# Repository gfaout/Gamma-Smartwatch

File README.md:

# Gamma-Smartwatch
Smartwatch designed in Summer of 2020

Version A (basic version):

Top Board Unfilled:

Top Board Filled:

Bottom Board Unfilled:

Bottom Board Filled:

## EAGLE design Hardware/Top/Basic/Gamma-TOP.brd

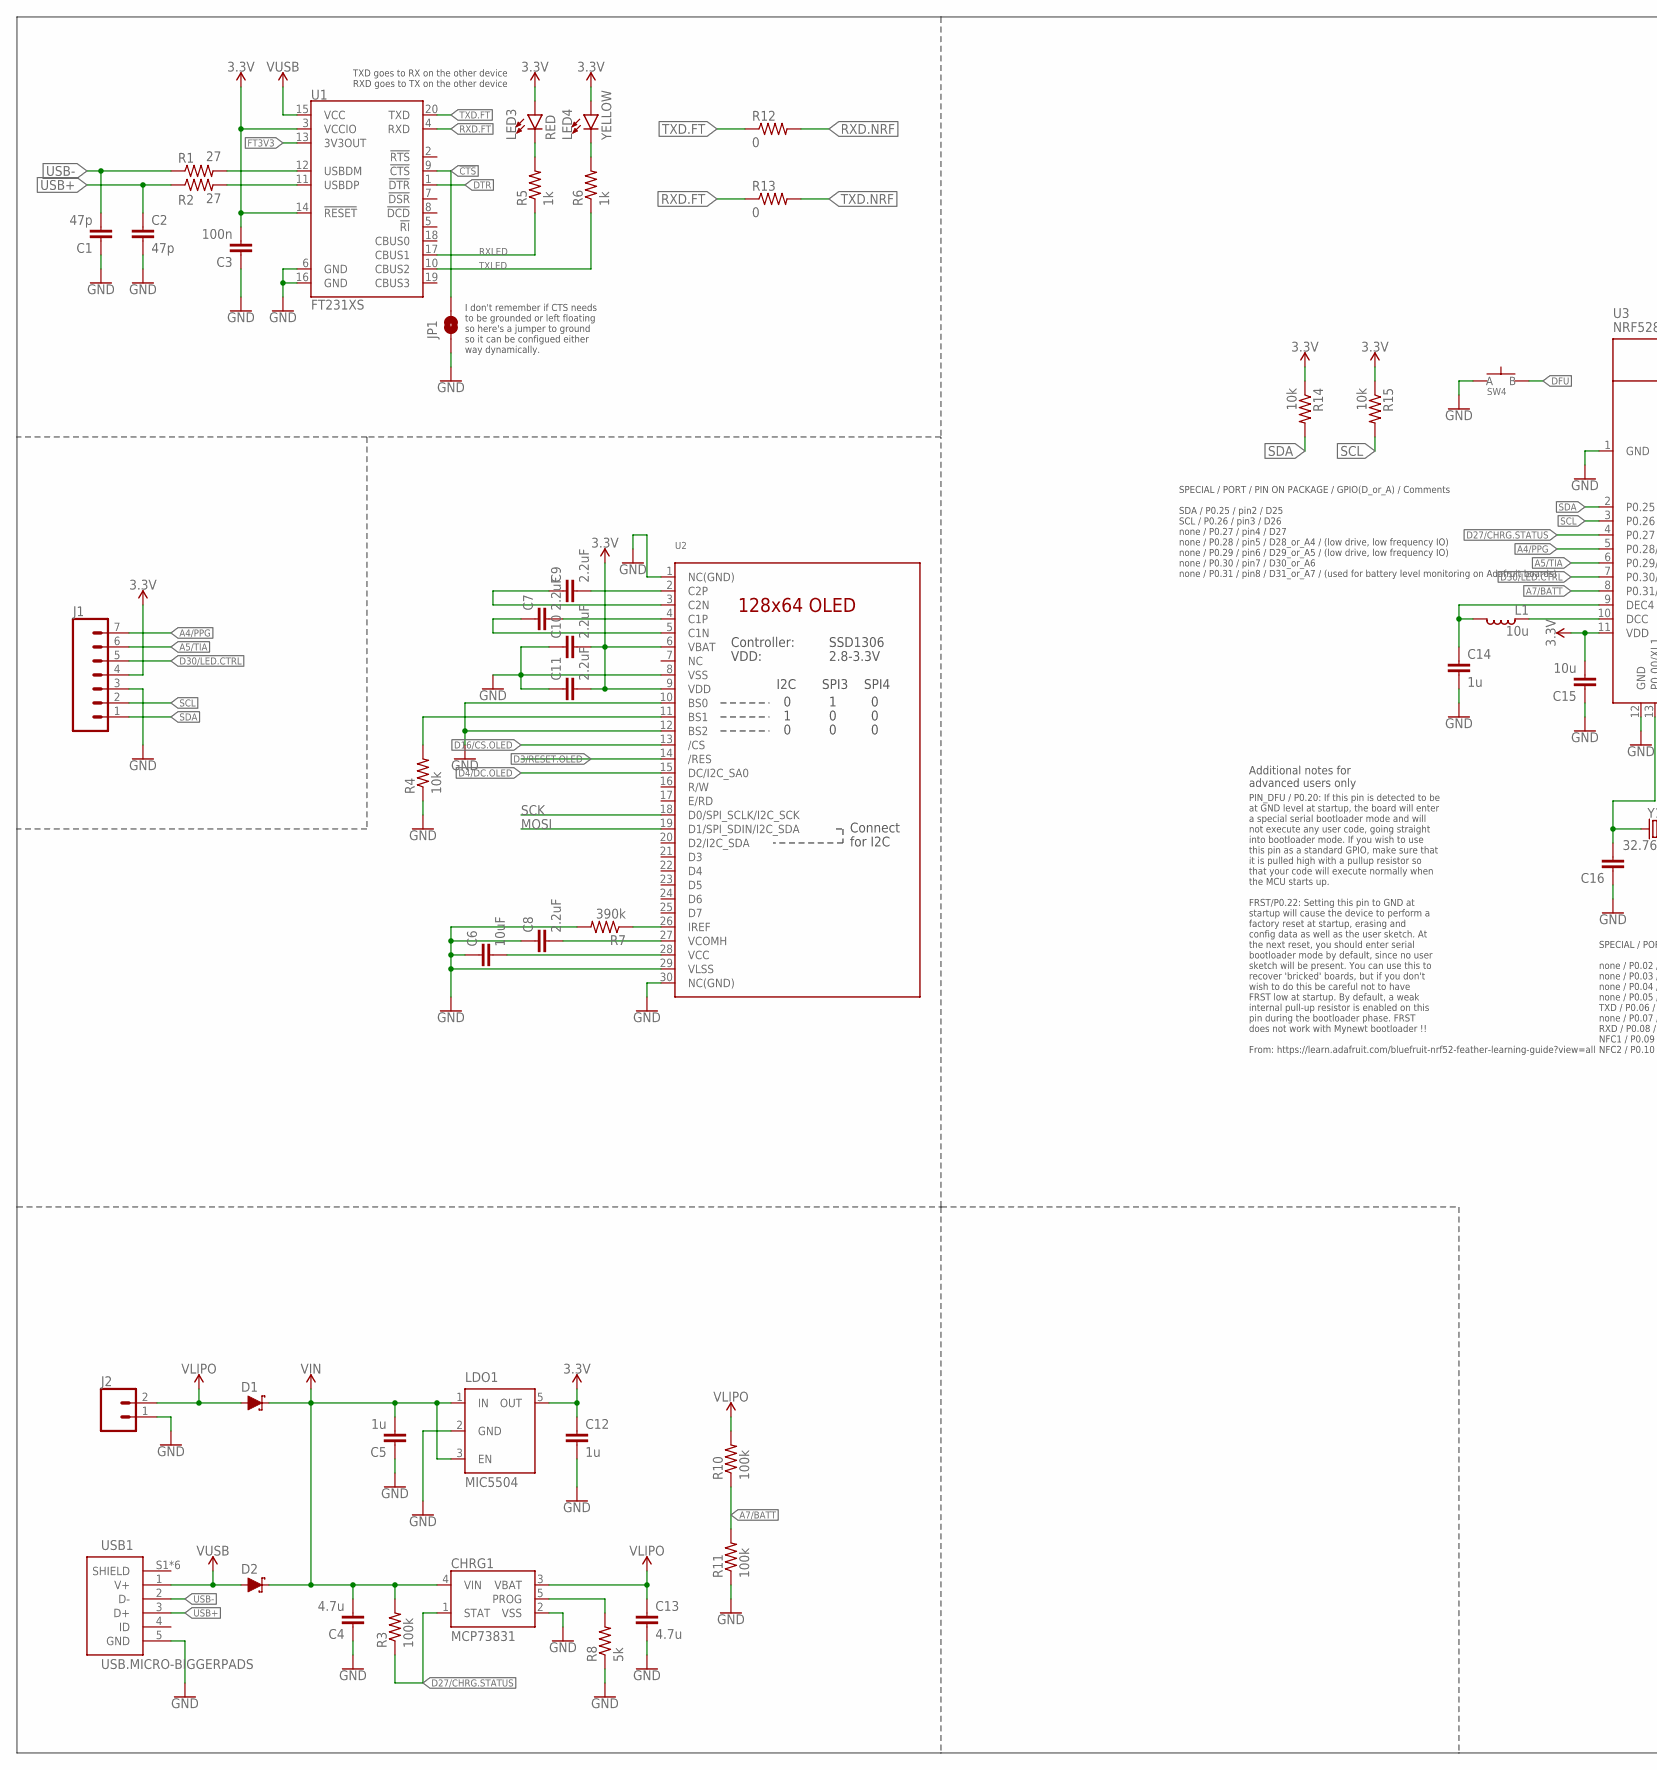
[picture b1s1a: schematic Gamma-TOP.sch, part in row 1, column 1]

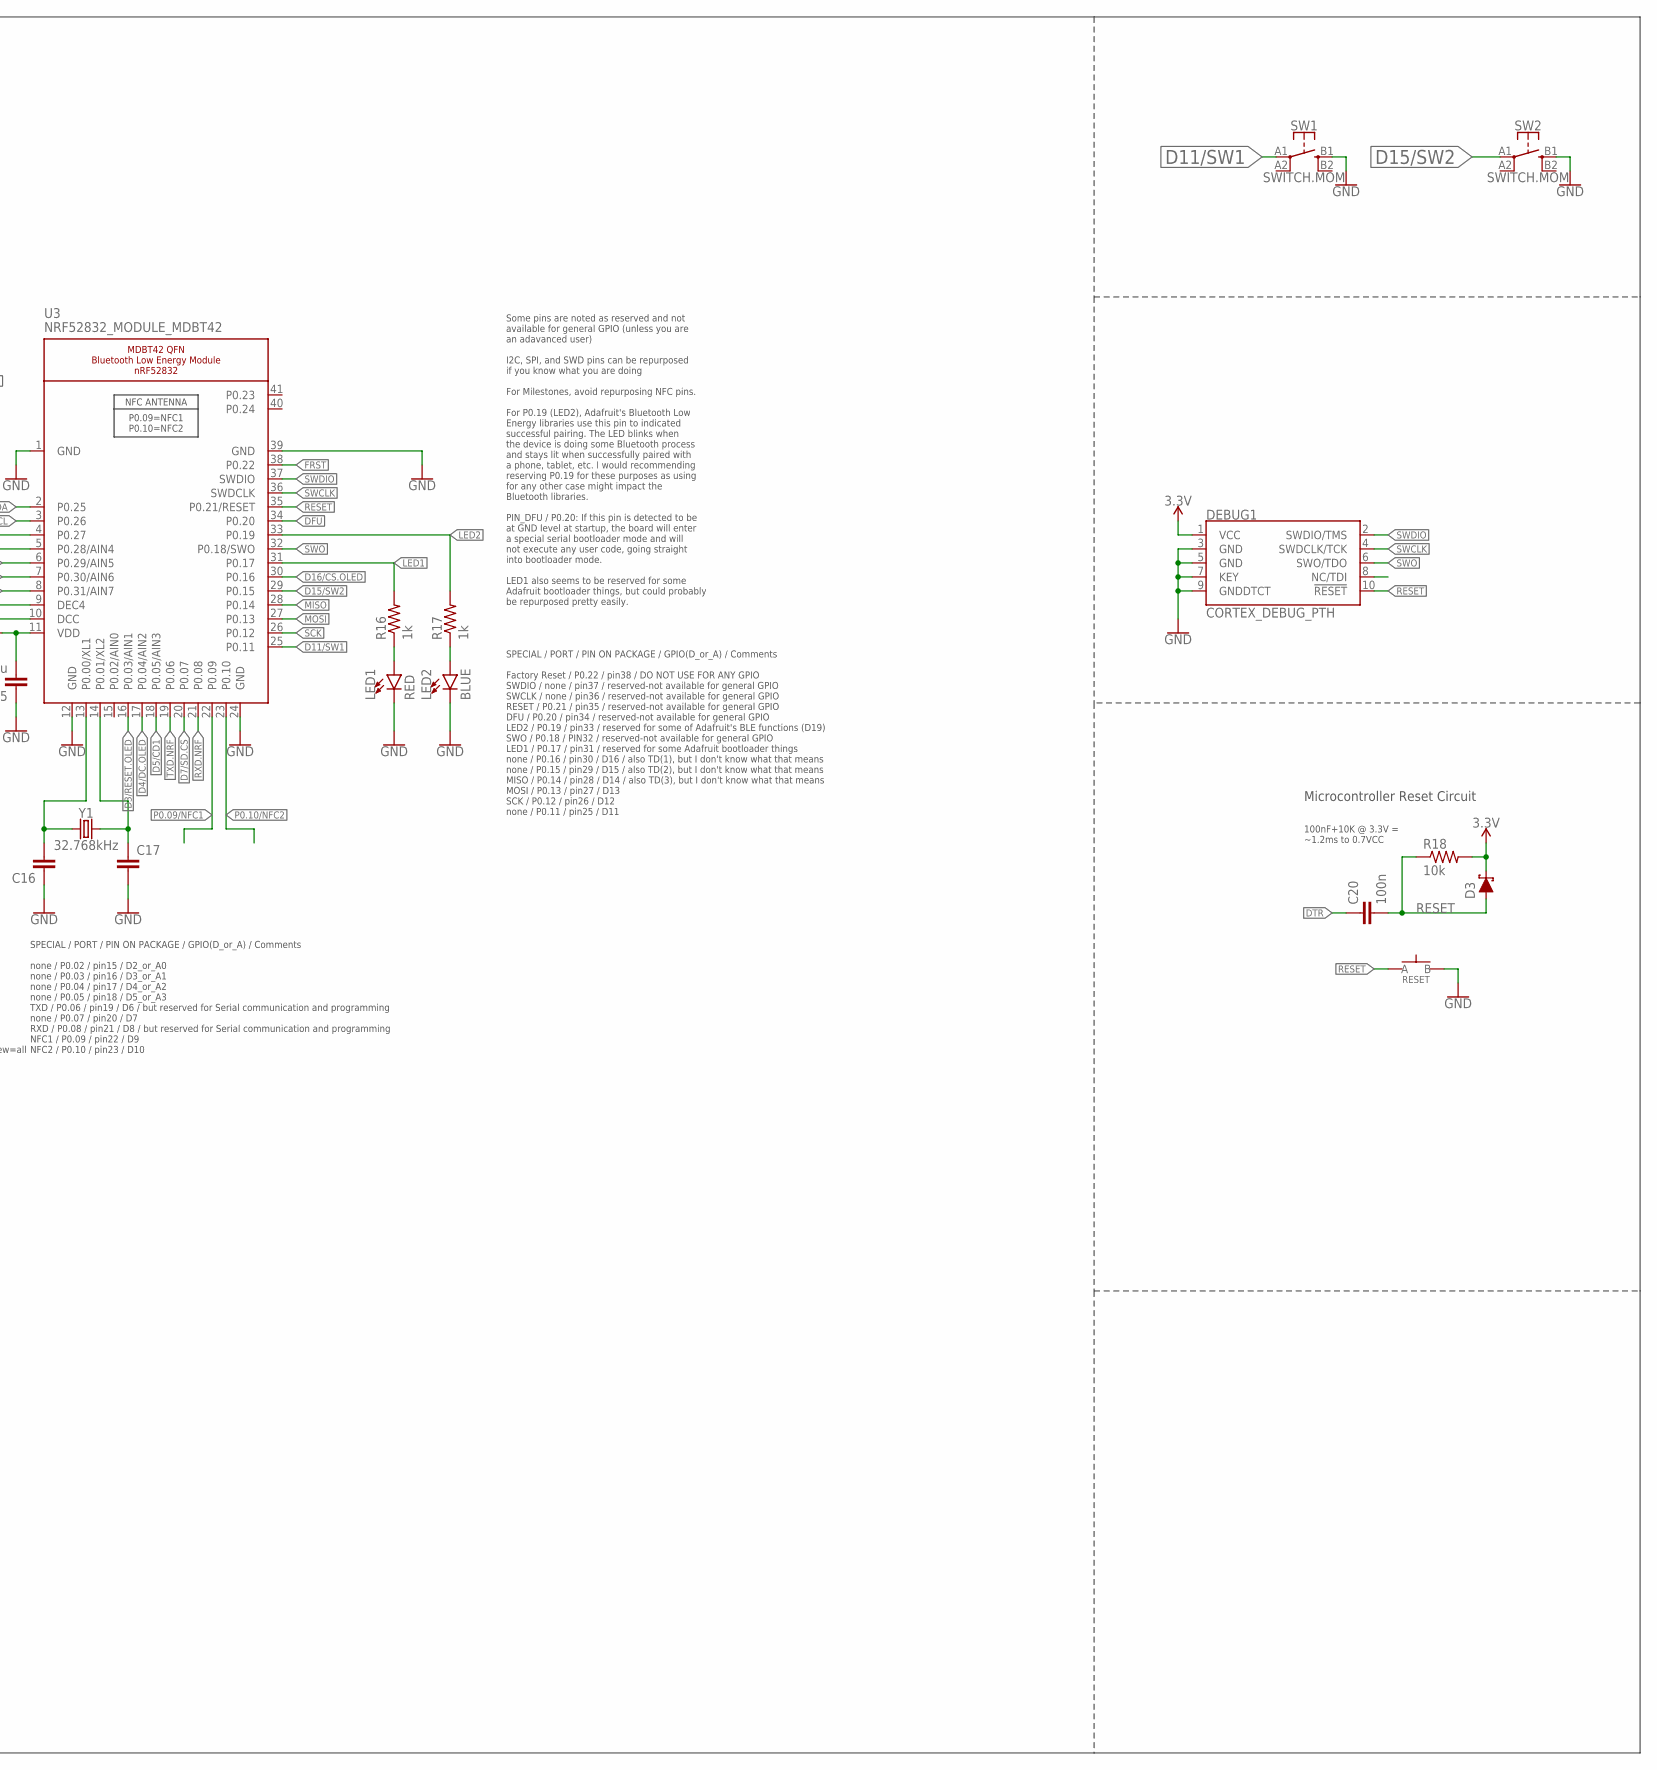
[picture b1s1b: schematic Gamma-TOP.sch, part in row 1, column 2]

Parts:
C1, C2: 47p; C0603
C3, C20: 100n; C0603
C4, C13: 4.7u; C0603
C5, C12, C14: 1u; C0603
C6: 10uF; C0603
C7, C9, C10, C11: 2.2uF; C0402
C8: 2.2uF; C0603
C15: 10u; C0805
C16, C17: CAPACITOR0603; C0603
CHRG1: MCP73831; SOT23-5
D1, D2, D3: SCHOTTKY-USC; USC
DEBUG1: CORTEX_DEBUG_PTH; 2X5-PTH-1.27MM
J1: CONN_07-1.27MM; 1X07_1.27MM
J2: CONN_02; 1X02
JP1: JUMPER-SMT_2_NO_SILK; SMT-JUMPER_2_NO_SILK
L1: 10u; L0603
LDO1: MIC5504; SOT23-5
LED1, LED3: RED; LED-0603
LED2: BLUE; LED-0603
LED4: YELLOW; LED-0603
R1, R2: 27; R0603
R3, R10, R11: 100k; R0603
R4, R14, R15, R18: 10k; R0603
R5, R6, R16, R17: 1k; R0603
R7: 390k; R0603
R8: 5k; R0603
R12, R13: 0; R0603
RESET: SPST-PTS830GG140-COPY.1-3; BUTTON-GULLWING
SW1, SW2: SWITCH.MOM; TACTILE_SWITCH_SMD_6.2MM_TALL
SW4: SPST-PTS830GG140-COPY.1-3; BUTTON-GULLWING
U1: FT231XS; SSOP20_L
U2: DISP_OLED_UG-2864HSWEG01-NO-WRAPAROUND; UG-2864HSWEG01_0.96IN_NO-WRAPAROUND
U3: NRF52832_MODULE_MDBT42; BLE_MODULE_RAYTAC_MDBT42
USB1: USB.MICRO-BIGGERPADS; USB-MICRO-01.BIGGERPADS
Y1: 32.768kHz; 2-SMD.NOLEAD.2.0MMTO1.2MM

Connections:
3.3V: C3.2, C10.2, C11.2, C12.1, C15.2, D3.- (C), DEBUG1.1 (VCC), J1.4, LDO1.5 (OUT), LED3.A, LED4.A, R14.1, R15.1, R18.2, U1.3 (VCCIO), U1.14 (!RESET), U2.6 (VBAT), U2.9 (VDD), U3.11 (VDD)
!CTS: JP1.2, U1.9 (!CTS)
A4/PPG: J1.7, U3.5 (P0.28/AIN4)
A5/TIA: J1.6, U3.6 (P0.29/AIN5)
A7/BATT: R10.1, R11.2, U3.8 (P0.31/AIN7)
D3/RESET.OLED: U2.14 (/RES), U3.16 (P0.03/AIN1)
D4/DC.OLED: U2.15 (DC/I2C_SA0), U3.17 (P0.04/AIN2)
D5/CD1: U3.18 (P0.05/AIN3)
D7/SD.CS: U3.20 (P0.07)
D11/SW1: SW1.A1 (1), U3.25 (P0.11)
D15/SW2: SW2.A1 (1), U3.29 (P0.15)
D16/CS.OLED: U2.13 (/CS), U3.30 (P0.16)
D27/CHRG.STATUS: CHRG1.1 (STAT), R3.1, U3.4 (P0.27)
D30/LED.CTRL: J1.5, U3.7 (P0.30/AIN6)
DFU: SW4.3 (B), U3.34 (P0.20)
DTR: C20.1, U1.1 (!DTR)
FRST: U3.38 (P0.22)
FT3V3: U1.13 (3V3OUT)
GND: C1.1, C2.2, C3.1, C4.1, C5.1, C6.1, C8.1, C10.1, C11.1, C12.2, C13.2, C14.2, C15.1, C16.1, C17.2, CHRG1.2 (VSS), DEBUG1.3 (GND), DEBUG1.5 (GND), DEBUG1.7 (KEY), DEBUG1.9 (GNDDTCT), J1.3, J2.1, JP1.1, LDO1.2 (GND), LED1.C, LED2.C, R4.1, R7.2, R8.1, R11.1, RESET.3 (B), SW1.B1 (3), SW2.B1 (3), SW4.1 (A), U1.6 (GND), U1.16 (GND), U2.1 (NC(GND)), U2.8 (VSS), U2.10 (BS0), U2.12 (BS2), U2.29 (VLSS), U2.30 (NC(GND)), U3.1 (GND), U3.12 (GND), U3.24 (GND), U3.39 (GND), USB1.5 (GND)
LED1: R16.2, U3.31 (P0.17)
LED2: R17.2, U3.33 (P0.19)
MISO: U3.28 (P0.14)
MOSI: U2.19 (D1/SPI_SDIN/I2C_SDA), U3.27 (P0.13)
unnamed: R4.2, U2.11 (BS1)
unnamed: R7.1, U2.26 (IREF)
unnamed: C9.2, U2.2 (C2P)
unnamed: C16.2, U3.13 (P0.00/XL1), Y1.P$1 (1)
unnamed: C9.1, U2.3 (C2N)
unnamed: C17.1, U3.14 (P0.01/XL2), Y1.P$2 (2)
unnamed: C7.2, U2.4 (C1P)
unnamed: C7.1, U2.5 (C1N)
unnamed: LED1.A, R16.1
unnamed: LED2.A, R17.1
unnamed: L1.1, U3.10 (DCC)
unnamed: C14.1, L1.2, U3.9 (DEC4)
unnamed: C6.2, U2.28 (VCC)
unnamed: C8.2, U2.27 (VCOMH)
unnamed: CHRG1.5 (PROG), R8.2
unnamed: R1.2, U1.12 (USBDM)
unnamed: R2.2, U1.11 (USBDP)
unnamed: LED3.C, R5.2
unnamed: LED4.C, R6.2
P0.09/NFC1: U3.22 (P0.09)
P0.10/NFC2: U3.23 (P0.10)
RESET: C20.2, D3.+ (A), DEBUG1.10 (!RESET), R18.1, RESET.1 (A), U3.35 (P0.21/RESET)
RXD.FT: R13.1, U1.4 (RXD)
RXD.NRF: R12.2, U3.21 (P0.08)
RXLED: R5.1, U1.17 (CBUS1)
SCK: U2.18 (D0/SPI_SCLK/I2C_SCK), U3.26 (P0.12)
SCL: J1.2, R15.2, U3.3 (P0.26)
SDA: J1.1, R14.2, U3.2 (P0.25)
SWCLK: DEBUG1.4 (SWDCLK/TCK), U3.36 (SWDCLK)
SWDIO: DEBUG1.2 (SWDIO/TMS), U3.37 (SWDIO)
SWO: DEBUG1.6 (SWO/TDO), U3.32 (P0.18/SWO)
TXD.FT: R12.1, U1.20 (TXD)
TXD.NRF: R13.2, U3.19 (P0.06)
TXLED: R6.1, U1.10 (CBUS2)
USB+: C2.1, R2.1, USB1.3 (D+)
USB-: C1.2, R1.1, USB1.2 (D-)
VIN: C4.2, C5.2, CHRG1.4 (VIN), D1.- (C), D2.- (C), LDO1.1 (IN), LDO1.3 (EN), R3.2
VLIPO: C13.1, CHRG1.3 (VBAT), D1.+ (A), J2.2, R10.2
V_USB: D2.+ (A), U1.15 (VCC), USB1.1 (V+)

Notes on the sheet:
Microcontroller Reset Circuit
100nF+10K @ 3.3V = ~1.2ms to 0.7VCC
SPECIAL / PORT / PIN ON PACKAGE / GPIO(D_or_A) / Comments SDA / P0.25 / pin2 / D25 SCL / P0.26 / pin3 / D26 none / P0.27 / pin4 / D27 none / P0.28 / pin5 / D28_or_A4 / (low drive, low frequency IO) none / P0.29 / pin6 / D29_or_A5 / (low drive, low frequency IO) none / P0.30 / pin7 / D30_or_A6 none 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
SPECIAL / PORT / PIN ON PACKAGE / GPIO(D_or_A) / Comments none / P0.02 / pin15 / D2_or_A0 none / P0.03 / pin16 / D3_or_A1 none / P0.04 / pin17 / D4_or_A2 none / P0.05 / pin18 / D5_or_A3 TXD / P0.06 / pin19 / D6 / but reserved for Serial communication and programming none / P0.07 / pin20 / D7 RXD / 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
SPECIAL / PORT / PIN ON PACKAGE / GPIO(D_or_A) / Comments Factory Reset / P0.22 / pin38 / DO NOT USE FOR ANY GPIO SWDIO / none / pin37 / reserved-not available for general GPIO SWCLK / none / pin36 / reserved-not available for general GPIO RESET / P0.21 / pin35 / reserved-not available for general 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
Some pins are noted as reserved and not available for general GPIO (unless you are an adavanced user) I2C, SPI, and SWD pins can be repurposed if you know what you are doing For Milestones, avoid repurposing NFC pins. For P0.19 (LED2), Adafruit's Bluetooth Low Energy libraries use this pin to indic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
PIN_DFU / P0.20: If this pin is detected to be at GND level at startup, the board will enter a special serial bootloader mode and will not execute any user code, going straight into bootloader mode. If you wish to use this pin as a standard GPIO, make sure that it is pulled high with a pullup resis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
Additional notes for advanced users only
TXD goes to RX on the other device RXD goes to TX on the other device
I don't remember if CTS needs to be grounded or left floating so here's a jumper to ground so it can be configued either way dynamically.

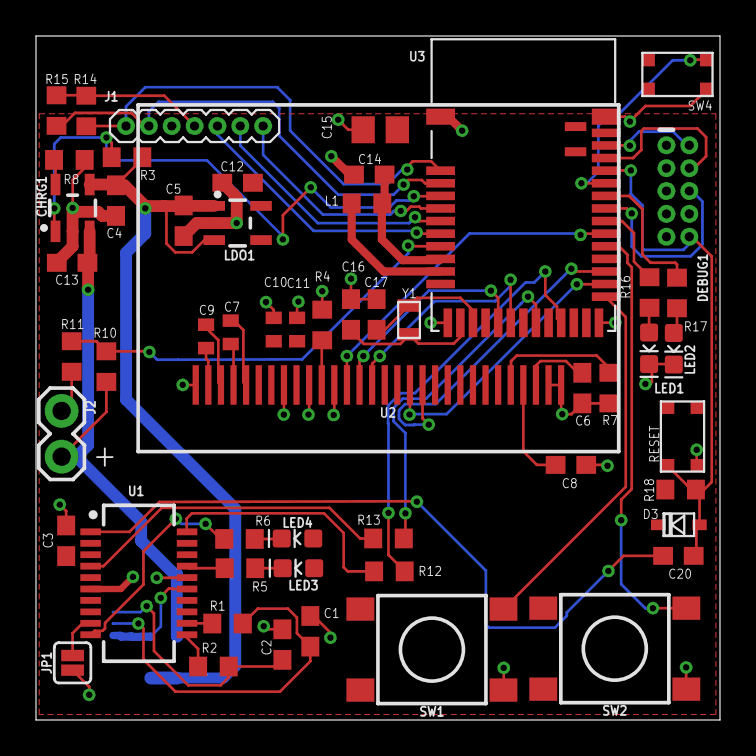
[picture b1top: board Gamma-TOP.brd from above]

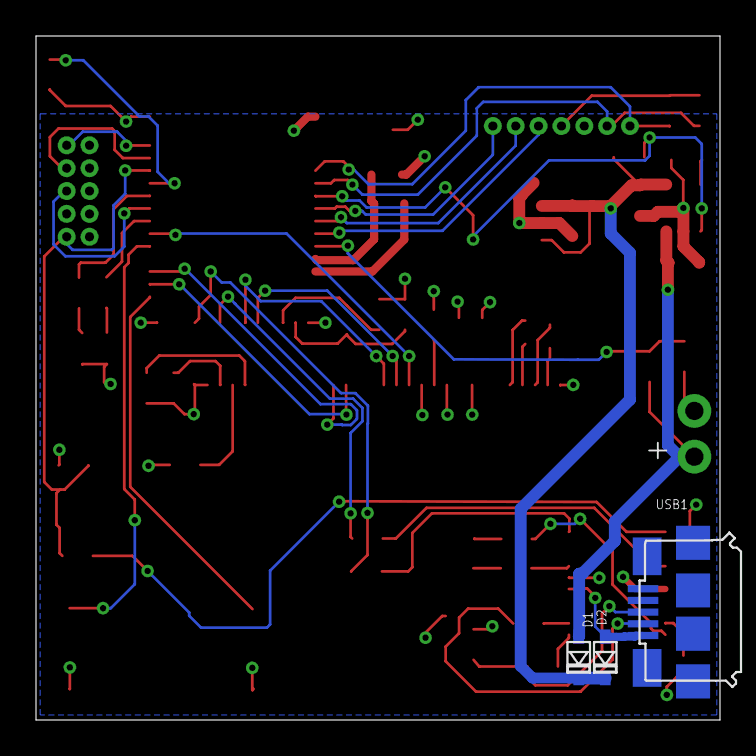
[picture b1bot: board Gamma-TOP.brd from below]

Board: 2 copper layers, 38.0 x 38.0 mm, 58 parts (3 on the bottom side), 55 nets.

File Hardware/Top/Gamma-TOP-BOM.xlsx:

Gamma Smartwatch Top Board -- Revision A / Gautam Fotedar |  |  |  |  |  |  |  |  |  |  | Total | 0 | Total (in Bulk) | 0
BOM # | Comment | Designator | Description | Mounting Type | Package | Manufacturer | Manufacturer Part Number | Supplier | Supplier Part Number | Price per unit | Quantity | Total | Per 100 | Total
1 | 47 pF Capacitor | C1,C2 |  |  |  |  |  |  |  |  | 2 | 0 |  | 0
2 | 27 ohm resistor | R1,R2 |  |  |  |  |  |  |  |  | 2 | 0 |  | 0
3 | 100 nF Capacitor | C3, C19, C20 |  |  |  |  |  |  |  |  | 3 | 0 |  | 0
4 | FT231XS USB Serial | U1 |  |  |  |  |  |  |  |  | 1 | 0 |  | 0
5 | SMT-JUMPER_2_NO_SILK (Version 1) | JP1 |  |  |  |  |  |  |  |  | 1 | 0 |  | 0
6 | 1k Resistor | R5, R6, R16, R17 |  |  |  |  |  |  |  |  | 4 | 0 |  | 0
7 | Red LED | LED1, LED3 |  |  |  |  |  |  |  |  | 2 | 0 |  | 0
8 | Yellow LED | LED4 |  |  |  |  |  |  |  |  | 1 | 0 |  | 0
9 | 0 ohm resistor (not sure if needed) | R12, R13 |  |  |  |  |  |  |  |  | 2 | 0 |  | 0
10 | CONN_07-1.27MM (CONN_07) | J1 |  |  |  |  |  |  |  |  | 1 | 0 |  | 0
11 | OLED UG-2864HSWEG01 | U2 |  |  |  |  |  |  |  |  | 1 | 0 |  | 0
12 | 2.2 uF 0402 Capacitor | C7, C9, C10, C11 |  |  |  |  |  |  |  |  | 4 | 0 |  | 0
13 | 10k resistor | R4, R14, R15, R18 |  |  |  |  |  |  |  |  | 4 | 0 |  | 0
14 | 390k resistor | R7 |  |  |  |  |  |  |  |  | 1 | 0 |  | 0
15 | 2.2 uF 0603 Capacitor | C8 |  |  |  |  |  |  |  |  | 1 | 0 |  | 0
16 | 10 uF 0603 Capacitor | C6, C15 |  |  |  |  |  |  |  |  | 2 | 0 |  | 0
17 | CONN_02 for Power Management | J2 |  |  |  |  |  |  |  |  | 1 | 0 |  | 0
18 | Schottky Diode | D1,D2, D3 |  |  |  |  |  |  |  |  | 3 | 0 |  | 0
19 | 1 uF 0603 capacitor | C5,C12, C14 |  |  |  |  |  |  |  |  | 3 | 0 |  | 0
20 | MIC5504 Voltage Regulator | LDO1 |  |  |  |  |  |  |  |  | 1 | 0 |  | 0
21 | 4.7 uF Capacitor | C4, C13 |  |  |  |  |  |  |  |  | 2 | 0 |  | 0
22 | 100K Resistor | R3, R10, R11 |  |  |  |  |  |  |  |  | 3 | 0 |  | 0
23 | MCP73831 T Li-Ion, Li-Pol Controller | CHRG1 |  |  |  |  |  |  |  |  | 1 | 0 |  | 0
24 | 5k resistor | R8 |  |  |  |  |  |  |  |  | 1 | 0 |  | 0
25 | FT24C64A EEPROM | U5 |  |  |  |  |  |  |  |  | 1 | 0 |  | 0
26 | 120 pF Capacitor | C18, C21 |  |  |  |  |  |  |  |  | 2 | 0 |  | 0
27 | 2.1 uH NFC Antenna | NFCANTENNA |  |  |  | Molex | 1462360151 |  |  |  | 1 | 0 |  | 0
28 | SPST-PTS830GG140 | RESET |  |  |  |  |  |  |  |  | 1 | 0 |  | 0
29 | Cortex Debug Connector - 10 pin | DEBUG1 |  |  |  |  |  |  |  |  | 1 | 0 |  | 0
30 | SWITCH.MOM (TACTILE_SWITCH_SMD_6.2MM_TALL) | SW1, SW2 |  |  |  |  |  |  |  |  | 2 | 0 |  | 0
31 | DFU SPST-PTS830GG140 | SW4 |  |  |  |  |  |  |  |  | 1 | 0 |  | 0
32 | 10 uH Inductor | L1 |  |  |  |  |  |  |  |  | 1 | 0 |  | 0
33 | Valuelesss capacitors | C16, C17 |  |  |  |  |  |  |  |  | 2 | 0 |  | 0
34 | CRYSTALECS-.327-12.5-12-C-TR (CRYSTAL) (32.768kHz) | Y1 |  |  |  |  |  |  |  |  | 1 | 0 |  | 0
35 | Blue LED | LED2 |  |  |  |  |  |  |  |  | 1 | 0 |  | 0
36 | NRF52832_MODULE_MDBT42 | U3 |  |  |  |  |  |  |  |  | 1 | 0 |  | 0

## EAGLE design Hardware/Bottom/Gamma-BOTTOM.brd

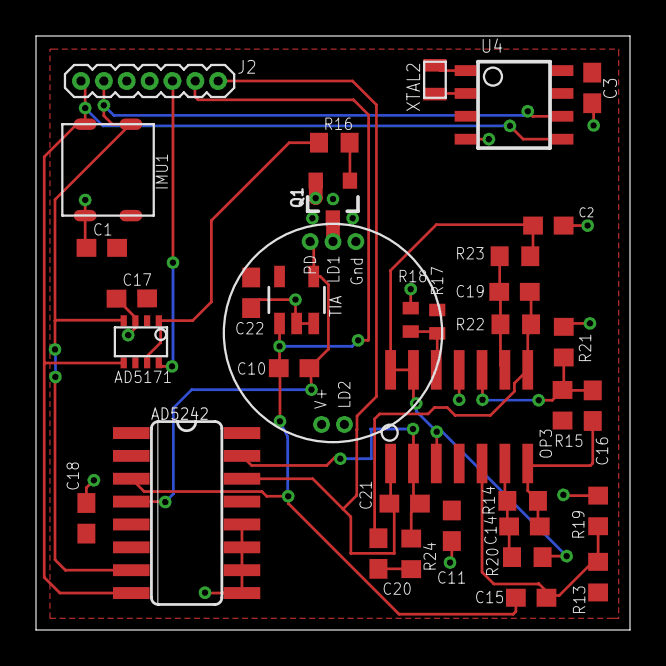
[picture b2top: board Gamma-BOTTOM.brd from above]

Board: 2 copper layers, 33.0 x 33.0 mm, 36 parts (0 on the bottom side), 23 nets.

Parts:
AD5171: AD5171; SOT-23-8
AD5242: AD5242-SO16; SO16
C1, C2, C10, C11, C17, C18, C22: 100n; C0603
C3: 1u; C0603
C14, C19: 2.2n; C0603
C15, C16: 2.2u; C0603
C20: 22u; C0603
C21: 22n; C0603
IMU1: LSM6DS3_CAST
J2: 1X07_1.27MM
OP3: SO14
Q1: SOT23-3
R13, R15, R19, R21: 220k; R0603
R14, R22: 10M; R0603
R16: R0603
R17, R18: 10k; R0402
R20, R23: 1M; R0603
R24: 10k; R0603
TIA: SOT23-5
U4: PCF8523; SO8
U$3: PPG.MODULE.2
XTAL2: 32.7680kHz; 2-SMD.NOLEAD.2.0MMTO1.2MM

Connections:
3.3V: AD5171.2, AD5171.6, AD5242.5, AD5242.6, C1.2, C3.1, C11.2, C17.2, C18.2, C22.2, IMU1.2, J2.4, OP3.4, R13.2, R15.2, R17.2, TIA.5, U4.8, U$3.V+
A4/PPG: AD5242.14, C21.2, J2.7, OP3.1
A5/TIA: AD5242.3, C10.2, C15.1, J2.6, TIA.1
D30/LED.CTRL: AD5171.8, J2.5
G.W2: AD5242.15, C21.1, OP3.2, R24.1
GND: AD5171.3, AD5242.9, AD5242.10, AD5242.11, AD5242.12, C1.1, C2.1, C3.2, C11.1, C17.1, C18.1, C22.1, IMU1.1, J2.3, OP3.11, Q1.2, R18.1, R19.1, R21.1, TIA.2, TIA.3, U4.4, U$3.GND
LED.C: Q1.3, U$3.LD1
unnamed: U4.2, XTAL2.P$1
unnamed: U4.1, XTAL2.P$2
unnamed: Q1.1, R16.2
unnamed: AD5171.1, AD5171.7, R16.1
unnamed: OP3.12, R17.1, R18.2
unnamed: C15.2, OP3.5, R13.1, R19.2
unnamed: C14.2, OP3.6, R14.1, R20.2
unnamed: C14.1, C16.1, OP3.7, R14.2
unnamed: C16.2, OP3.10, R15.1, R21.2
unnamed: C19.2, OP3.9, R22.1, R23.2
unnamed: C19.1, C20.1, OP3.8, R22.2
unnamed: C20.2, R24.2
PD.C: AD5242.4, C10.1, TIA.4, U$3.PD
SCL: AD5171.4, AD5242.7, IMU1.3, J2.2, U4.6
SDA: AD5171.5, AD5242.8, IMU1.4, J2.1, U4.5
VREF: C2.2, OP3.3, OP3.13, OP3.14, R20.1, R23.1

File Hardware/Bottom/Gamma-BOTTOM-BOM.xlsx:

Gamma Smartwatch Bottom Board -- Revision A / Gautam Fotedar |  |  |  |  |  |  |  |  |  |  | Total | 0 | Total (in Bulk) | 0
BOM # | Comment | Designator | Description | Mounting Type | Package | Manufacturer | Manufacturer Part Number | Supplier | Supplier Part Number | Price per unit | Quantity | Total | Per 100 | Total
1 | CONN_07-1.27MM | J2 |  |  |  |  |  |  |  |  | 1 | 0 |  | 0
2 | LSM6DS3_CAST | IMU1 |  |  |  |  |  |  |  |  | 1 | 0 |  | 0
3 | 100 nF Capacitor | C1,C2,C10,C17,C18,C22 |  |  |  |  |  |  |  |  | 6 | 0 |  | 0
4 | 1 uF Capacitor | C3 |  |  |  |  |  |  |  |  | 1 | 0 |  | 0
5 | CRYSTALECS-.327-12.5-12-C-TR (CRYSTAL) (32.7680kHz) | XTAL2 |  |  |  |  |  |  |  |  | 1 | 0 |  | 0
6 | PCF8523 | U4 |  |  |  |  |  |  |  |  | 1 | 0 |  | 0
7 | 0.05 spaced Header Pins | J2 | Connector Header Through Hole 50 position 0.050" (1.27mm) |  |  | Sullins Connector Solutions | GRPB501VWVN-RC |  | S9014E-50-ND |  | 1 | 0 |  | 0
8 | AD5171 | AD5172 |  |  |  |  |  |  |  |  | 1 | 0 |  | 0
9 | AD5242 | AD5243 |  |  |  |  |  |  |  |  | 1 | 0 |  | 0
10 | TIA | TIA |  |  |  |  |  |  |  |  | 1 | 0 |  | 0
11 | NPN-Generic | Q1 |  |  |  |  |  |  |  |  | 1 | 0 |  | 0
12 | Resistor (valueless) | R16 |  |  |  |  |  |  |  |  | 1 | 0 |  | 0
13 | 1M Resistor | R20,R23 |  |  |  |  |  |  |  |  | 2 | 0 |  | 0
14 | 2.2n Capacitor | C14,C19 |  |  |  |  |  |  |  |  | 2 | 0 |  | 0
15 | 10M Resistor | R14,R22 |  |  |  |  |  |  |  |  | 2 | 0 |  | 0
16 | 10k Resistor | R17,R18,R24 |  |  |  |  |  |  |  |  | 3 | 0 |  | 0
17 | 220k resistor | R13,R19,R21 |  |  |  |  |  |  |  |  | 3 | 0 |  | 0
18 | Op amp | OP3 |  |  |  |  |  |  |  |  | 1 | 0 |  | 0
19 | 22n capacitor | C21 |  |  |  |  |  |  |  |  | 1 | 0 |  | 0
20 | 22u capacitor | C20 |  |  |  |  |  |  |  |  | 1 | 0 |  | 0
21 | 2.2u capacitor | C15 |  |  |  |  |  |  |  |  | 1 | 0 |  | 0

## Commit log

2020-05-28 Adding featurelist.txt
2020-05-29 Updating the potential feature list
2020-06-04 updated the name of the feature list document
2020-06-04 Completed Organization of Smartwatch Repository
2020-06-04 First update to the Top board
2020-06-05 Fixed an overlap of two components
2020-06-11 Update to Top and Bottom Boards. Top is not complete as of yet, and the bottom is ready for a check. Routing not performed yet
2020-06-28 Finished Bottom Board as of Take 003
2020-07-01 Finished Take 004 up until deletion of NFC capacitors. Board partially routed
2020-07-02 This is the routing as of Take 006 before the removal of the SD Card
2020-07-02 Partway through Take 007
2020-07-02 Pushed Changes to where I'm at (Take 007)
2020-07-03 Take 007 35:16, before I attempt to move the power circuit on bottom of Top board out to the outside regions
2020-07-03 Finished with Preliminary Version A of Smartwatch as of end of Take 008 video
2020-07-04 First stage of prototyping
2020-07-04 Adding reference images of Version A of the smartwatch before functionalities added
2020-07-04 Modified existing image files
2020-07-04 Updated file structure
2020-07-04 Removed long directory name
2020-07-08 Updated PPG module BOM and board/schematic. Note: the board and schematic were taken directly from the Kick Jr repository without modification
2020-08-17 Changes including: Creation of final board designs, firmware updates, creation of NFC antenna device in Eagle
2020-08-17 Updated file names and completed preliminary BOM for each board
2020-08-24 Fixed organization of Smartwatch old and new files
2020-10-28 small fixes
2021-10-14 Added README for software section
2021-10-14 Added more to README
2021-10-14 Added timeline
2021-10-14 Added license
